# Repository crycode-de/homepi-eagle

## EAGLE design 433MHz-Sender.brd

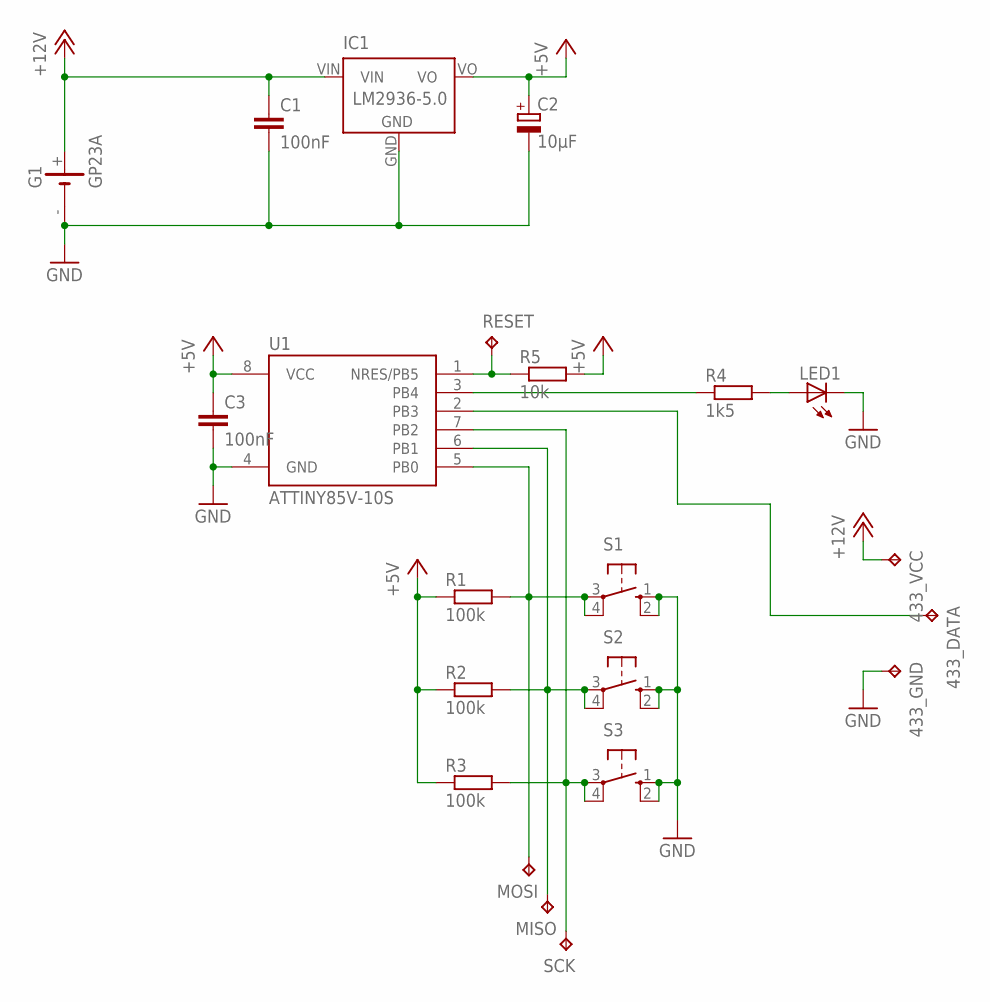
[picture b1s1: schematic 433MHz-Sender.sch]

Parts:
433_DATA, 433_GND, 433_VCC: TPPAD1-13; P1-13
C1, C3: 100nF; C025-025X050
C2: 10µF; E2-4
G1: GP23A
IC1: LM2936-5.0; TO92-INLINE
LED1: LED3MM
MISO: TPPAD1-13; P1-13
MOSI: TPPAD1-13; P1-13
R1, R2, R3: 100k; 0204/5
R4: 1k5; 0204/5
R5: 10k; 0204/5
RESET: TPPAD1-13; P1-13
S1, S2, S3: 10-XX; B3F-10XX
SCK: TPPAD1-13; P1-13
U1: ATTINY85V-10S; SOIC8_EIAJ_208MIL

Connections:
+5V: C2.+, C3.1, IC1.VO, R1.1, R2.1, R3.1, R5.2, U1.8 (VCC)
+12V: 433_VCC.TP, C1.1, G1.+, IC1.VIN
GND: 433_GND.TP, C1.2, C2.-, C3.2, G1.-, IC1.GND, LED1.K (C), S1.1 (S), S1.2 (S1), S2.1 (S), S2.2 (S1), S3.1 (S), S3.2 (S1), U1.4 (GND)
unnamed: 433_DATA.TP, U1.2 (PB3)
unnamed: R5.1, RESET.TP, U1.1 (NRES/PB5)
unnamed: MOSI.TP, R1.2, S1.3, S1.4 (P1), U1.5 (PB0)
unnamed: MISO.TP, R2.2, S2.3, S2.4 (P1), U1.6 (PB1)
unnamed: R3.2, S3.3, S3.4 (P1), SCK.TP, U1.7 (PB2)
unnamed: R4.1, U1.3 (PB4)
unnamed: LED1.A, R4.2

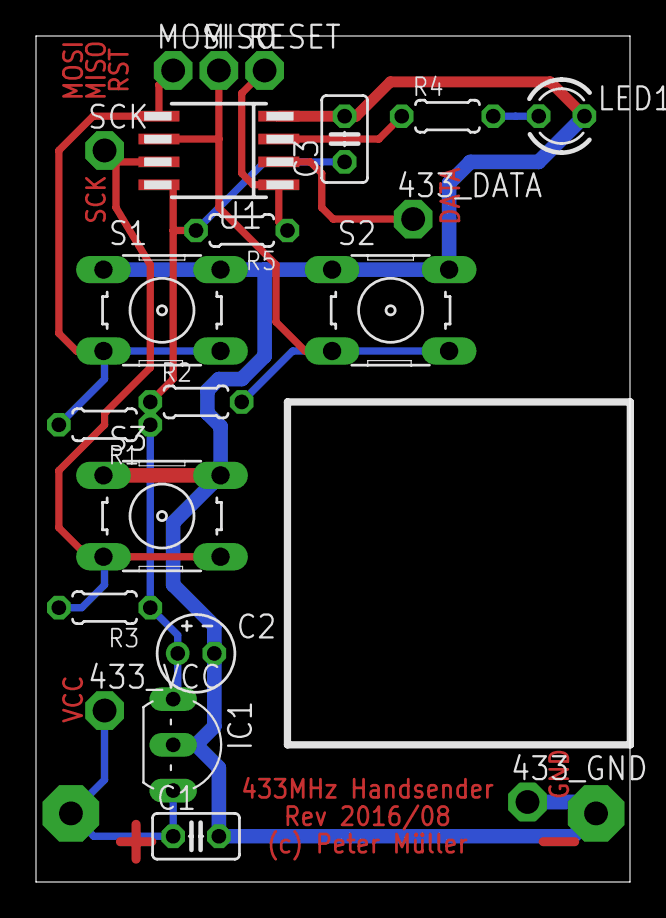
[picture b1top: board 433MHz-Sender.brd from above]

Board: 2 copper layers, 33.0 x 47.0 mm, 22 parts (1 on the bottom side), 10 nets.

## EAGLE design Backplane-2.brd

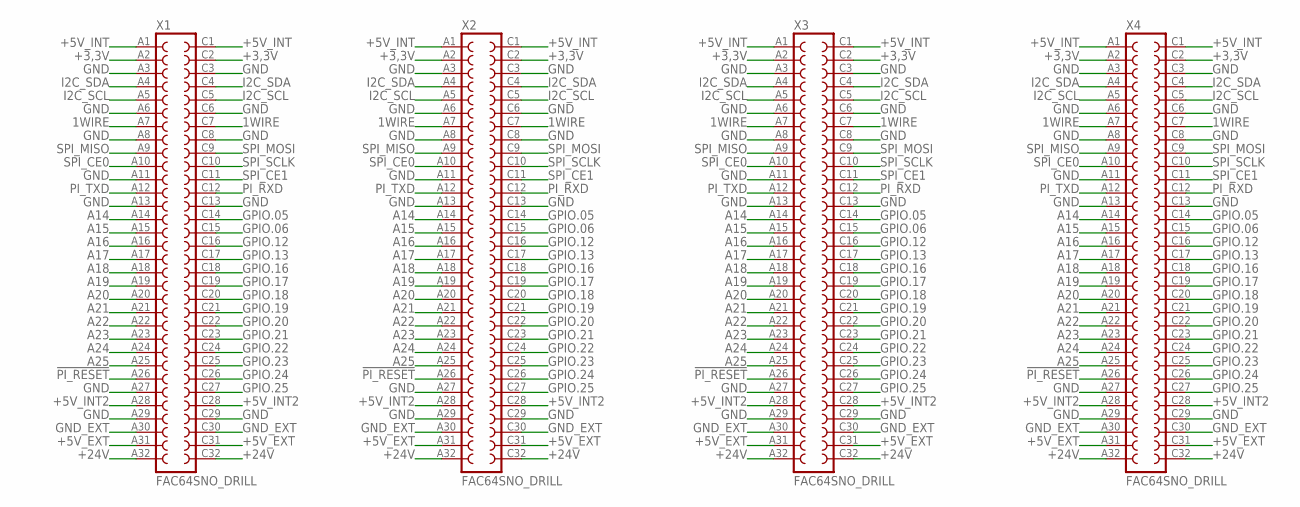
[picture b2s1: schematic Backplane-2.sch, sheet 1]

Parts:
X1, X2, X3, X4: FAC64SNO_DRILL; FAC64S_NO_DRILL

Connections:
1WIRE: X1.A7, X1.C7, X2.A7, X2.C7, X3.A7, X3.C7, X4.A7, X4.C7; also elsewhere on the board
!PI_RESET: X1.A26, X2.A26, X3.A26, X4.A26; also elsewhere on the board
+3,3V: X1.A2, X1.C2, X2.A2, X2.C2, X3.A2, X3.C2, X4.A2, X4.C2; also elsewhere on the board
+5V_EXT: X1.A31, X1.C31, X2.A31, X2.C31, X3.A31, X3.C31, X4.A31, X4.C31; also elsewhere on the board
+5V_INT: X1.A1, X1.C1, X2.A1, X2.C1, X3.A1, X3.C1, X4.A1, X4.C1; also elsewhere on the board
+5V_INT2: X1.A28, X1.C28, X2.A28, X2.C28, X3.A28, X3.C28, X4.A28, X4.C28; also elsewhere on the board
+24V: X1.A32, X1.C32, X2.A32, X2.C32, X3.A32, X3.C32, X4.A32, X4.C32; also elsewhere on the board
A14: X1.A14, X2.A14, X3.A14, X4.A14; also elsewhere on the board
A15: X1.A15, X2.A15, X3.A15, X4.A15; also elsewhere on the board
A16: X1.A16, X2.A16, X3.A16, X4.A16; also elsewhere on the board
A17: X1.A17, X2.A17, X3.A17, X4.A17; also elsewhere on the board
A18: X1.A18, X2.A18, X3.A18, X4.A18; also elsewhere on the board
A19: X1.A19, X2.A19, X3.A19, X4.A19; also elsewhere on the board
A20: X1.A20, X2.A20, X3.A20, X4.A20; also elsewhere on the board
A21: X1.A21, X2.A21, X3.A21, X4.A21; also elsewhere on the board
A22: X1.A22, X2.A22, X3.A22, X4.A22; also elsewhere on the board
A23: X1.A23, X2.A23, X3.A23, X4.A23; also elsewhere on the board
A24: X1.A24, X2.A24, X3.A24, X4.A24; also elsewhere on the board
A25: X1.A25, X2.A25, X3.A25, X4.A25; also elsewhere on the board
GND: X1.A3, X1.A6, X1.A8, X1.A11, X1.A13, X1.A27, X1.A29, X1.C3, X1.C6, X1.C8, X1.C13, X1.C29, X2.A3, X2.A6, X2.A8, X2.A11, X2.A13, X2.A27, X2.A29, X2.C3, X2.C6, X2.C8, X2.C13, X2.C29, X3.A3, X3.A6, X3.A8, X3.A11, X3.A13, X3.A27, X3.A29, X3.C3, X3.C6, X3.C8, X3.C13, X3.C29, X4.A3, X4.A6, X4.A8, X4.A11, X4.A13, X4.A27, X4.A29, X4.C3, X4.C6, X4.C8, X4.C13, X4.C29; also elsewhere on the board
GND_EXT: X1.A30, X1.C30, X2.A30, X2.C30, X3.A30, X3.C30, X4.A30, X4.C30; also elsewhere on the board
GPIO.05: X1.C14, X2.C14, X3.C14, X4.C14; also elsewhere on the board
GPIO.06: X1.C15, X2.C15, X3.C15, X4.C15; also elsewhere on the board
GPIO.12: X1.C16, X2.C16, X3.C16, X4.C16; also elsewhere on the board
GPIO.13: X1.C17, X2.C17, X3.C17, X4.C17; also elsewhere on the board
GPIO.16: X1.C18, X2.C18, X3.C18, X4.C18; also elsewhere on the board
GPIO.17: X1.C19, X2.C19, X3.C19, X4.C19; also elsewhere on the board
GPIO.18: X1.C20, X2.C20, X3.C20, X4.C20; also elsewhere on the board
GPIO.19: X1.C21, X2.C21, X3.C21, X4.C21; also elsewhere on the board
GPIO.20: X1.C22, X2.C22, X3.C22, X4.C22; also elsewhere on the board
GPIO.21: X1.C23, X2.C23, X3.C23, X4.C23; also elsewhere on the board
GPIO.22: X1.C24, X2.C24, X3.C24, X4.C24; also elsewhere on the board
GPIO.23: X1.C25, X2.C25, X3.C25, X4.C25; also elsewhere on the board
GPIO.24: X1.C26, X2.C26, X3.C26, X4.C26; also elsewhere on the board
GPIO.25: X1.C27, X2.C27, X3.C27, X4.C27; also elsewhere on the board
I2C_SCL: X1.A5, X1.C5, X2.A5, X2.C5, X3.A5, X3.C5, X4.A5, X4.C5; also elsewhere on the board
I2C_SDA: X1.A4, X1.C4, X2.A4, X2.C4, X3.A4, X3.C4, X4.A4, X4.C4; also elsewhere on the board
PI_RXD: X1.C12, X2.C12, X3.C12, X4.C12; also elsewhere on the board
PI_TXD: X1.A12, X2.A12, X3.A12, X4.A12; also elsewhere on the board
SPI_CE0: X1.A10, X2.A10, X3.A10, X4.A10; also elsewhere on the board
SPI_CE1: X1.C11, X2.C11, X3.C11, X4.C11; also elsewhere on the board
SPI_MISO: X1.A9, X2.A9, X3.A9, X4.A9; also elsewhere on the board
SPI_MOSI: X1.C9, X2.C9, X3.C9, X4.C9; also elsewhere on the board
SPI_SCLK: X1.C10, X2.C10, X3.C10, X4.C10; also elsewhere on the board

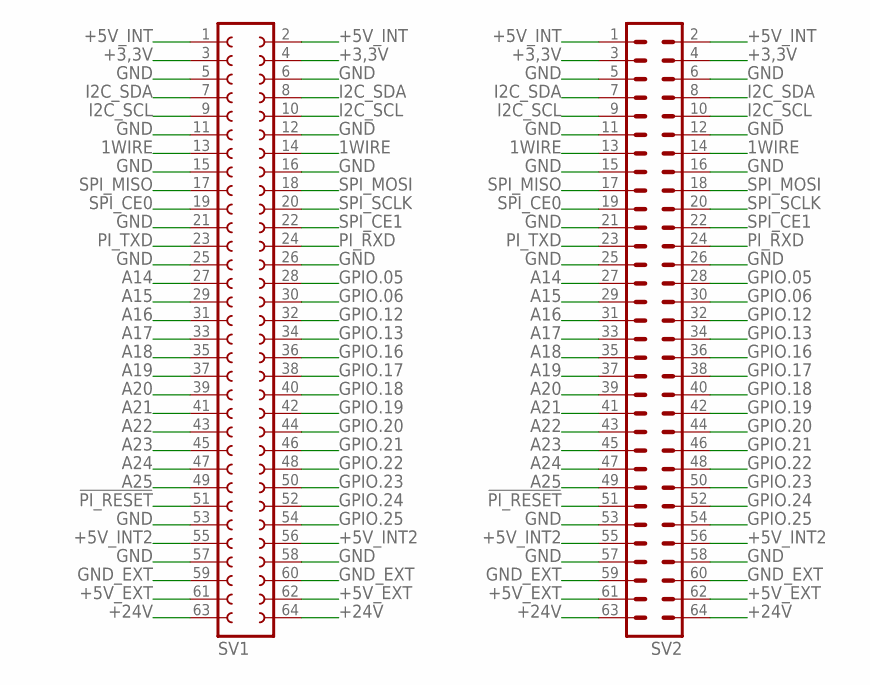
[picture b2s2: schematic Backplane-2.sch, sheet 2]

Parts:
SV1: FE32-2W
SV2: MA32-2W

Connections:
1WIRE: SV1.13, SV1.14, SV2.13, SV2.14; also elsewhere on the board
!PI_RESET: SV1.51, SV2.51; also elsewhere on the board
+3,3V: SV1.3, SV1.4, SV2.3, SV2.4; also elsewhere on the board
+5V_EXT: SV1.61, SV1.62, SV2.61, SV2.62; also elsewhere on the board
+5V_INT: SV1.1, SV1.2, SV2.1, SV2.2; also elsewhere on the board
+5V_INT2: SV1.55, SV1.56, SV2.55, SV2.56; also elsewhere on the board
+24V: SV1.63, SV1.64, SV2.63, SV2.64; also elsewhere on the board
A14: SV1.27, SV2.27; also elsewhere on the board
A15: SV1.29, SV2.29; also elsewhere on the board
A16: SV1.31, SV2.31; also elsewhere on the board
A17: SV1.33, SV2.33; also elsewhere on the board
A18: SV1.35, SV2.35; also elsewhere on the board
A19: SV1.37, SV2.37; also elsewhere on the board
A20: SV1.39, SV2.39; also elsewhere on the board
A21: SV1.41, SV2.41; also elsewhere on the board
A22: SV1.43, SV2.43; also elsewhere on the board
A23: SV1.45, SV2.45; also elsewhere on the board
A24: SV1.47, SV2.47; also elsewhere on the board
A25: SV1.49, SV2.49; also elsewhere on the board
GND: SV1.5, SV1.6, SV1.11, SV1.12, SV1.15, SV1.16, SV1.21, SV1.25, SV1.26, SV1.53, SV1.57, SV1.58, SV2.5, SV2.6, SV2.11, SV2.12, SV2.15, SV2.16, SV2.21, SV2.25, SV2.26, SV2.53, SV2.57, SV2.58; also elsewhere on the board
GND_EXT: SV1.59, SV1.60, SV2.59, SV2.60; also elsewhere on the board
GPIO.05: SV1.28, SV2.28; also elsewhere on the board
GPIO.06: SV1.30, SV2.30; also elsewhere on the board
GPIO.12: SV1.32, SV2.32; also elsewhere on the board
GPIO.13: SV1.34, SV2.34; also elsewhere on the board
GPIO.16: SV1.36, SV2.36; also elsewhere on the board
GPIO.17: SV1.38, SV2.38; also elsewhere on the board
GPIO.18: SV1.40, SV2.40; also elsewhere on the board
GPIO.19: SV1.42, SV2.42; also elsewhere on the board
GPIO.20: SV1.44, SV2.44; also elsewhere on the board
GPIO.21: SV1.46, SV2.46; also elsewhere on the board
GPIO.22: SV1.48, SV2.48; also elsewhere on the board
GPIO.23: SV1.50, SV2.50; also elsewhere on the board
GPIO.24: SV1.52, SV2.52; also elsewhere on the board
GPIO.25: SV1.54, SV2.54; also elsewhere on the board
I2C_SCL: SV1.9, SV1.10, SV2.9, SV2.10; also elsewhere on the board
I2C_SDA: SV1.7, SV1.8, SV2.7, SV2.8; also elsewhere on the board
PI_RXD: SV1.24, SV2.24; also elsewhere on the board
PI_TXD: SV1.23, SV2.23; also elsewhere on the board
SPI_CE0: SV1.19, SV2.19; also elsewhere on the board
SPI_CE1: SV1.22, SV2.22; also elsewhere on the board
SPI_MISO: SV1.17, SV2.17; also elsewhere on the board
SPI_MOSI: SV1.18, SV2.18; also elsewhere on the board
SPI_SCLK: SV1.20, SV2.20; also elsewhere on the board

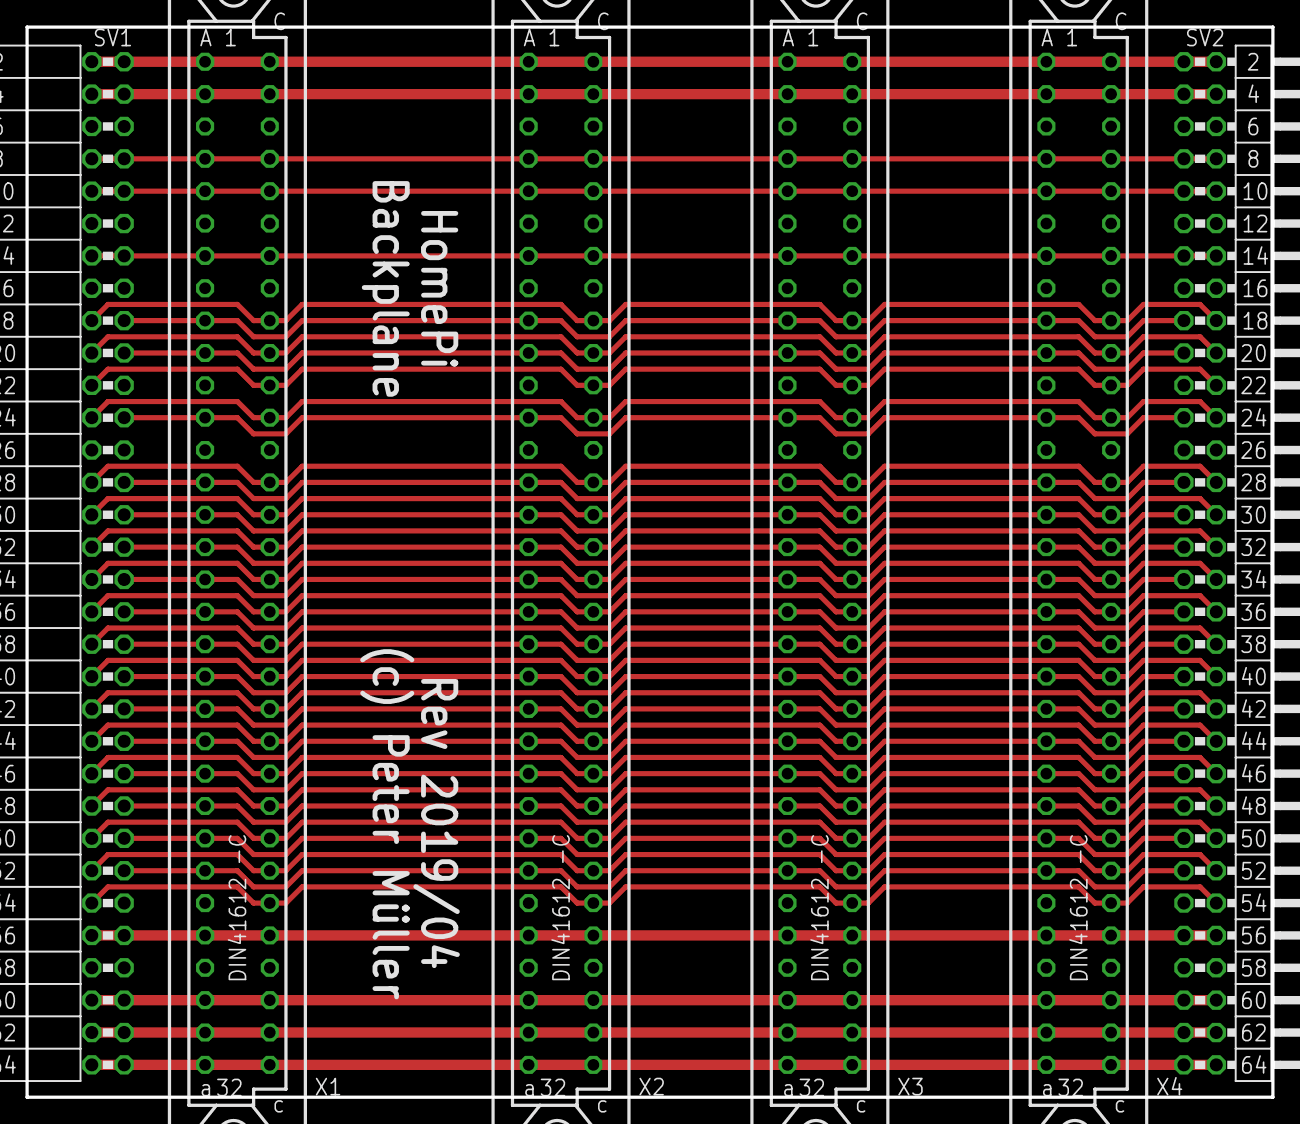
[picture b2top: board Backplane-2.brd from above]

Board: 2 copper layers, 97.8 x 84.0 mm, 6 parts (0 on the bottom side), 44 nets.

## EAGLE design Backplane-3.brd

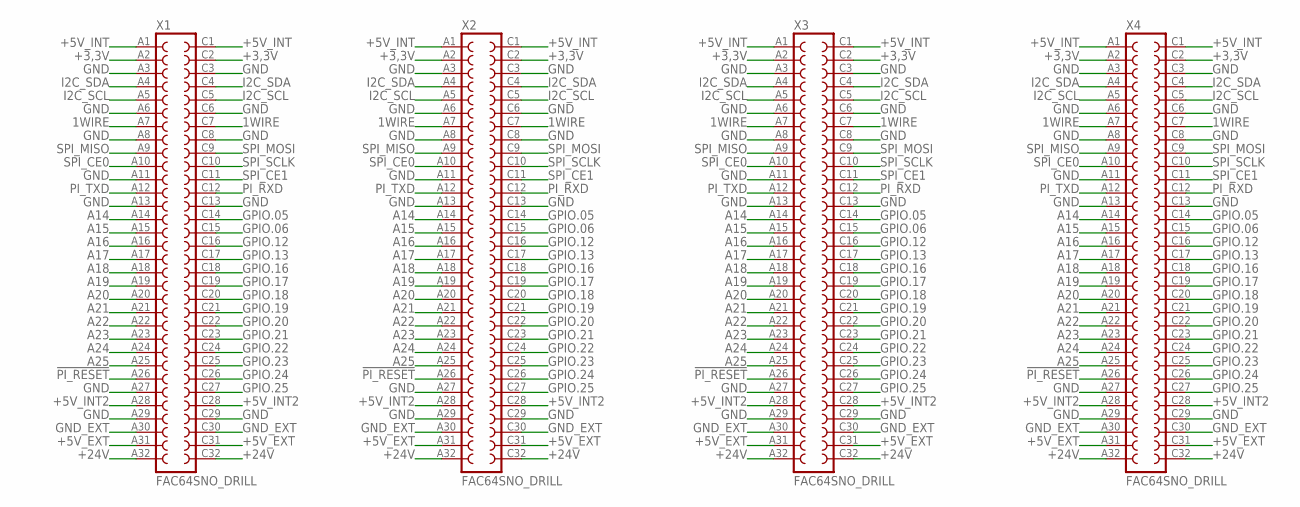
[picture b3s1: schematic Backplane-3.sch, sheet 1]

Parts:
X1, X2, X3, X4: FAC64SNO_DRILL; FAC64S_NO_DRILL

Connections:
1WIRE: X1.A7, X1.C7, X2.A7, X2.C7, X3.A7, X3.C7, X4.A7, X4.C7; also elsewhere on the board
!PI_RESET: X1.A26, X2.A26, X3.A26, X4.A26; also elsewhere on the board
+3,3V: X1.A2, X1.C2, X2.A2, X2.C2, X3.A2, X3.C2, X4.A2, X4.C2; also elsewhere on the board
+5V_EXT: X1.A31, X1.C31, X2.A31, X2.C31, X3.A31, X3.C31, X4.A31, X4.C31; also elsewhere on the board
+5V_INT: X1.A1, X1.C1, X2.A1, X2.C1, X3.A1, X3.C1, X4.A1, X4.C1; also elsewhere on the board
+5V_INT2: X1.A28, X1.C28, X2.A28, X2.C28, X3.A28, X3.C28, X4.A28, X4.C28; also elsewhere on the board
+24V: X1.A32, X1.C32, X2.A32, X2.C32, X3.A32, X3.C32, X4.A32, X4.C32; also elsewhere on the board
A14: X1.A14, X2.A14, X3.A14, X4.A14; also elsewhere on the board
A15: X1.A15, X2.A15, X3.A15, X4.A15; also elsewhere on the board
A16: X1.A16, X2.A16, X3.A16, X4.A16; also elsewhere on the board
A17: X1.A17, X2.A17, X3.A17, X4.A17; also elsewhere on the board
A18: X1.A18, X2.A18, X3.A18, X4.A18; also elsewhere on the board
A19: X1.A19, X2.A19, X3.A19, X4.A19; also elsewhere on the board
A20: X1.A20, X2.A20, X3.A20, X4.A20; also elsewhere on the board
A21: X1.A21, X2.A21, X3.A21, X4.A21; also elsewhere on the board
A22: X1.A22, X2.A22, X3.A22, X4.A22; also elsewhere on the board
A23: X1.A23, X2.A23, X3.A23, X4.A23; also elsewhere on the board
A24: X1.A24, X2.A24, X3.A24, X4.A24; also elsewhere on the board
A25: X1.A25, X2.A25, X3.A25, X4.A25; also elsewhere on the board
GND: X1.A3, X1.A6, X1.A8, X1.A11, X1.A13, X1.A27, X1.A29, X1.C3, X1.C6, X1.C8, X1.C13, X1.C29, X2.A3, X2.A6, X2.A8, X2.A11, X2.A13, X2.A27, X2.A29, X2.C3, X2.C6, X2.C8, X2.C13, X2.C29, X3.A3, X3.A6, X3.A8, X3.A11, X3.A13, X3.A27, X3.A29, X3.C3, X3.C6, X3.C8, X3.C13, X3.C29, X4.A3, X4.A6, X4.A8, X4.A11, X4.A13, X4.A27, X4.A29, X4.C3, X4.C6, X4.C8, X4.C13, X4.C29; also elsewhere on the board
GND_EXT: X1.A30, X1.C30, X2.A30, X2.C30, X3.A30, X3.C30, X4.A30, X4.C30; also elsewhere on the board
GPIO.05: X1.C14, X2.C14, X3.C14, X4.C14; also elsewhere on the board
GPIO.06: X1.C15, X2.C15, X3.C15, X4.C15; also elsewhere on the board
GPIO.12: X1.C16, X2.C16, X3.C16, X4.C16; also elsewhere on the board
GPIO.13: X1.C17, X2.C17, X3.C17, X4.C17; also elsewhere on the board
GPIO.16: X1.C18, X2.C18, X3.C18, X4.C18; also elsewhere on the board
GPIO.17: X1.C19, X2.C19, X3.C19, X4.C19; also elsewhere on the board
GPIO.18: X1.C20, X2.C20, X3.C20, X4.C20; also elsewhere on the board
GPIO.19: X1.C21, X2.C21, X3.C21, X4.C21; also elsewhere on the board
GPIO.20: X1.C22, X2.C22, X3.C22, X4.C22; also elsewhere on the board
GPIO.21: X1.C23, X2.C23, X3.C23, X4.C23; also elsewhere on the board
GPIO.22: X1.C24, X2.C24, X3.C24, X4.C24; also elsewhere on the board
GPIO.23: X1.C25, X2.C25, X3.C25, X4.C25; also elsewhere on the board
GPIO.24: X1.C26, X2.C26, X3.C26, X4.C26; also elsewhere on the board
GPIO.25: X1.C27, X2.C27, X3.C27, X4.C27; also elsewhere on the board
I2C_SCL: X1.A5, X1.C5, X2.A5, X2.C5, X3.A5, X3.C5, X4.A5, X4.C5; also elsewhere on the board
I2C_SDA: X1.A4, X1.C4, X2.A4, X2.C4, X3.A4, X3.C4, X4.A4, X4.C4; also elsewhere on the board
PI_RXD: X1.C12, X2.C12, X3.C12, X4.C12; also elsewhere on the board
PI_TXD: X1.A12, X2.A12, X3.A12, X4.A12; also elsewhere on the board
SPI_CE0: X1.A10, X2.A10, X3.A10, X4.A10; also elsewhere on the board
SPI_CE1: X1.C11, X2.C11, X3.C11, X4.C11; also elsewhere on the board
SPI_MISO: X1.A9, X2.A9, X3.A9, X4.A9; also elsewhere on the board
SPI_MOSI: X1.C9, X2.C9, X3.C9, X4.C9; also elsewhere on the board
SPI_SCLK: X1.C10, X2.C10, X3.C10, X4.C10; also elsewhere on the board

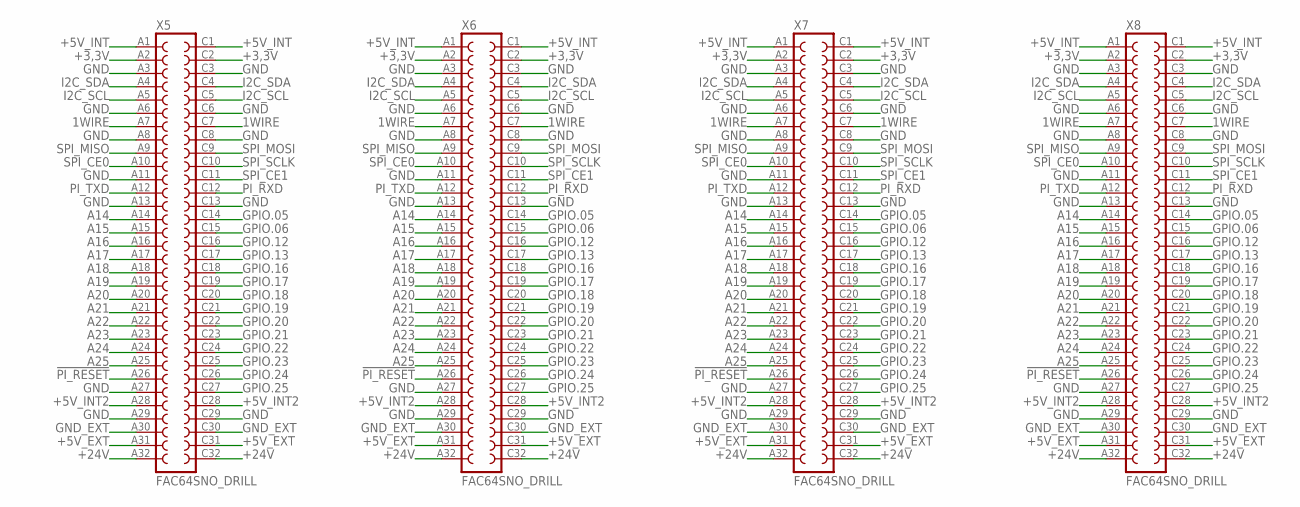
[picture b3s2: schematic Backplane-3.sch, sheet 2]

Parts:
X5, X6, X7, X8: FAC64SNO_DRILL; FAC64S_NO_DRILL

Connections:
1WIRE: X5.A7, X5.C7, X6.A7, X6.C7, X7.A7, X7.C7, X8.A7, X8.C7; also elsewhere on the board
!PI_RESET: X5.A26, X6.A26, X7.A26, X8.A26; also elsewhere on the board
+3,3V: X5.A2, X5.C2, X6.A2, X6.C2, X7.A2, X7.C2, X8.A2, X8.C2; also elsewhere on the board
+5V_EXT: X5.A31, X5.C31, X6.A31, X6.C31, X7.A31, X7.C31, X8.A31, X8.C31; also elsewhere on the board
+5V_INT: X5.A1, X5.C1, X6.A1, X6.C1, X7.A1, X7.C1, X8.A1, X8.C1; also elsewhere on the board
+5V_INT2: X5.A28, X5.C28, X6.A28, X6.C28, X7.A28, X7.C28, X8.A28, X8.C28; also elsewhere on the board
+24V: X5.A32, X5.C32, X6.A32, X6.C32, X7.A32, X7.C32, X8.A32, X8.C32; also elsewhere on the board
A14: X5.A14, X6.A14, X7.A14, X8.A14; also elsewhere on the board
A15: X5.A15, X6.A15, X7.A15, X8.A15; also elsewhere on the board
A16: X5.A16, X6.A16, X7.A16, X8.A16; also elsewhere on the board
A17: X5.A17, X6.A17, X7.A17, X8.A17; also elsewhere on the board
A18: X5.A18, X6.A18, X7.A18, X8.A18; also elsewhere on the board
A19: X5.A19, X6.A19, X7.A19, X8.A19; also elsewhere on the board
A20: X5.A20, X6.A20, X7.A20, X8.A20; also elsewhere on the board
A21: X5.A21, X6.A21, X7.A21, X8.A21; also elsewhere on the board
A22: X5.A22, X6.A22, X7.A22, X8.A22; also elsewhere on the board
A23: X5.A23, X6.A23, X7.A23, X8.A23; also elsewhere on the board
A24: X5.A24, X6.A24, X7.A24, X8.A24; also elsewhere on the board
A25: X5.A25, X6.A25, X7.A25, X8.A25; also elsewhere on the board
GND: X5.A3, X5.A6, X5.A8, X5.A11, X5.A13, X5.A27, X5.A29, X5.C3, X5.C6, X5.C8, X5.C13, X5.C29, X6.A3, X6.A6, X6.A8, X6.A11, X6.A13, X6.A27, X6.A29, X6.C3, X6.C6, X6.C8, X6.C13, X6.C29, X7.A3, X7.A6, X7.A8, X7.A11, X7.A13, X7.A27, X7.A29, X7.C3, X7.C6, X7.C8, X7.C13, X7.C29, X8.A3, X8.A6, X8.A8, X8.A11, X8.A13, X8.A27, X8.A29, X8.C3, X8.C6, X8.C8, X8.C13, X8.C29; also elsewhere on the board
GND_EXT: X5.A30, X5.C30, X6.A30, X6.C30, X7.A30, X7.C30, X8.A30, X8.C30; also elsewhere on the board
GPIO.05: X5.C14, X6.C14, X7.C14, X8.C14; also elsewhere on the board
GPIO.06: X5.C15, X6.C15, X7.C15, X8.C15; also elsewhere on the board
GPIO.12: X5.C16, X6.C16, X7.C16, X8.C16; also elsewhere on the board
GPIO.13: X5.C17, X6.C17, X7.C17, X8.C17; also elsewhere on the board
GPIO.16: X5.C18, X6.C18, X7.C18, X8.C18; also elsewhere on the board
GPIO.17: X5.C19, X6.C19, X7.C19, X8.C19; also elsewhere on the board
GPIO.18: X5.C20, X6.C20, X7.C20, X8.C20; also elsewhere on the board
GPIO.19: X5.C21, X6.C21, X7.C21, X8.C21; also elsewhere on the board
GPIO.20: X5.C22, X6.C22, X7.C22, X8.C22; also elsewhere on the board
GPIO.21: X5.C23, X6.C23, X7.C23, X8.C23; also elsewhere on the board
GPIO.22: X5.C24, X6.C24, X7.C24, X8.C24; also elsewhere on the board
GPIO.23: X5.C25, X6.C25, X7.C25, X8.C25; also elsewhere on the board
GPIO.24: X5.C26, X6.C26, X7.C26, X8.C26; also elsewhere on the board
GPIO.25: X5.C27, X6.C27, X7.C27, X8.C27; also elsewhere on the board
I2C_SCL: X5.A5, X5.C5, X6.A5, X6.C5, X7.A5, X7.C5, X8.A5, X8.C5; also elsewhere on the board
I2C_SDA: X5.A4, X5.C4, X6.A4, X6.C4, X7.A4, X7.C4, X8.A4, X8.C4; also elsewhere on the board
PI_RXD: X5.C12, X6.C12, X7.C12, X8.C12; also elsewhere on the board
PI_TXD: X5.A12, X6.A12, X7.A12, X8.A12; also elsewhere on the board
SPI_CE0: X5.A10, X6.A10, X7.A10, X8.A10; also elsewhere on the board
SPI_CE1: X5.C11, X6.C11, X7.C11, X8.C11; also elsewhere on the board
SPI_MISO: X5.A9, X6.A9, X7.A9, X8.A9; also elsewhere on the board
SPI_MOSI: X5.C9, X6.C9, X7.C9, X8.C9; also elsewhere on the board
SPI_SCLK: X5.C10, X6.C10, X7.C10, X8.C10; also elsewhere on the board

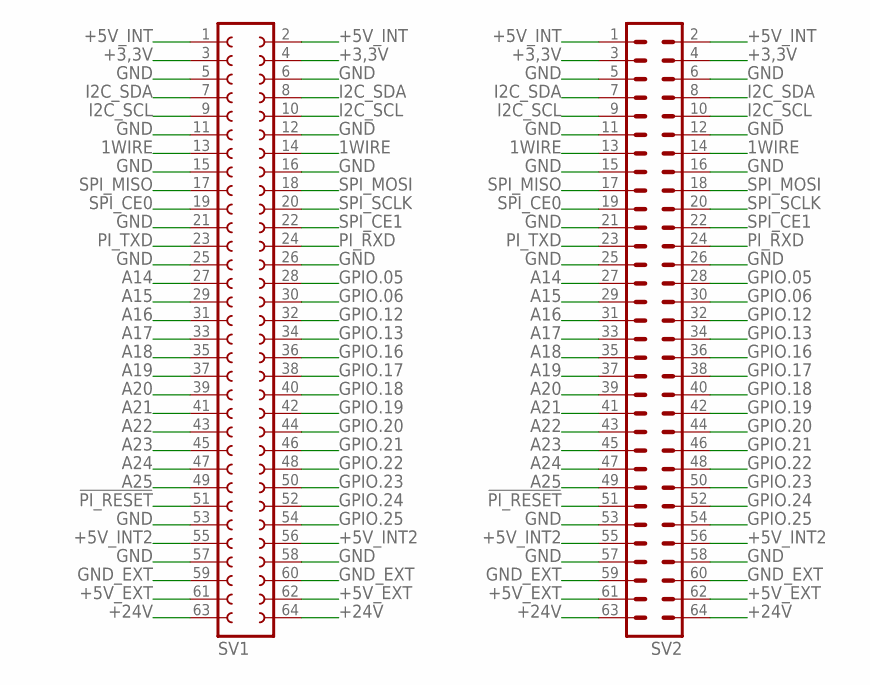
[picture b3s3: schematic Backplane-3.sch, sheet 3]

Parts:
SV1: FE32-2W
SV2: MA32-2W

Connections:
1WIRE: SV1.13, SV1.14, SV2.13, SV2.14; also elsewhere on the board
!PI_RESET: SV1.51, SV2.51; also elsewhere on the board
+3,3V: SV1.3, SV1.4, SV2.3, SV2.4; also elsewhere on the board
+5V_EXT: SV1.61, SV1.62, SV2.61, SV2.62; also elsewhere on the board
+5V_INT: SV1.1, SV1.2, SV2.1, SV2.2; also elsewhere on the board
+5V_INT2: SV1.55, SV1.56, SV2.55, SV2.56; also elsewhere on the board
+24V: SV1.63, SV1.64, SV2.63, SV2.64; also elsewhere on the board
A14: SV1.27, SV2.27; also elsewhere on the board
A15: SV1.29, SV2.29; also elsewhere on the board
A16: SV1.31, SV2.31; also elsewhere on the board
A17: SV1.33, SV2.33; also elsewhere on the board
A18: SV1.35, SV2.35; also elsewhere on the board
A19: SV1.37, SV2.37; also elsewhere on the board
A20: SV1.39, SV2.39; also elsewhere on the board
A21: SV1.41, SV2.41; also elsewhere on the board
A22: SV1.43, SV2.43; also elsewhere on the board
A23: SV1.45, SV2.45; also elsewhere on the board
A24: SV1.47, SV2.47; also elsewhere on the board
A25: SV1.49, SV2.49; also elsewhere on the board
GND: SV1.5, SV1.6, SV1.11, SV1.12, SV1.15, SV1.16, SV1.21, SV1.25, SV1.26, SV1.53, SV1.57, SV1.58, SV2.5, SV2.6, SV2.11, SV2.12, SV2.15, SV2.16, SV2.21, SV2.25, SV2.26, SV2.53, SV2.57, SV2.58; also elsewhere on the board
GND_EXT: SV1.59, SV1.60, SV2.59, SV2.60; also elsewhere on the board
GPIO.05: SV1.28, SV2.28; also elsewhere on the board
GPIO.06: SV1.30, SV2.30; also elsewhere on the board
GPIO.12: SV1.32, SV2.32; also elsewhere on the board
GPIO.13: SV1.34, SV2.34; also elsewhere on the board
GPIO.16: SV1.36, SV2.36; also elsewhere on the board
GPIO.17: SV1.38, SV2.38; also elsewhere on the board
GPIO.18: SV1.40, SV2.40; also elsewhere on the board
GPIO.19: SV1.42, SV2.42; also elsewhere on the board
GPIO.20: SV1.44, SV2.44; also elsewhere on the board
GPIO.21: SV1.46, SV2.46; also elsewhere on the board
GPIO.22: SV1.48, SV2.48; also elsewhere on the board
GPIO.23: SV1.50, SV2.50; also elsewhere on the board
GPIO.24: SV1.52, SV2.52; also elsewhere on the board
GPIO.25: SV1.54, SV2.54; also elsewhere on the board
I2C_SCL: SV1.9, SV1.10, SV2.9, SV2.10; also elsewhere on the board
I2C_SDA: SV1.7, SV1.8, SV2.7, SV2.8; also elsewhere on the board
PI_RXD: SV1.24, SV2.24; also elsewhere on the board
PI_TXD: SV1.23, SV2.23; also elsewhere on the board
SPI_CE0: SV1.19, SV2.19; also elsewhere on the board
SPI_CE1: SV1.22, SV2.22; also elsewhere on the board
SPI_MISO: SV1.17, SV2.17; also elsewhere on the board
SPI_MOSI: SV1.18, SV2.18; also elsewhere on the board
SPI_SCLK: SV1.20, SV2.20; also elsewhere on the board

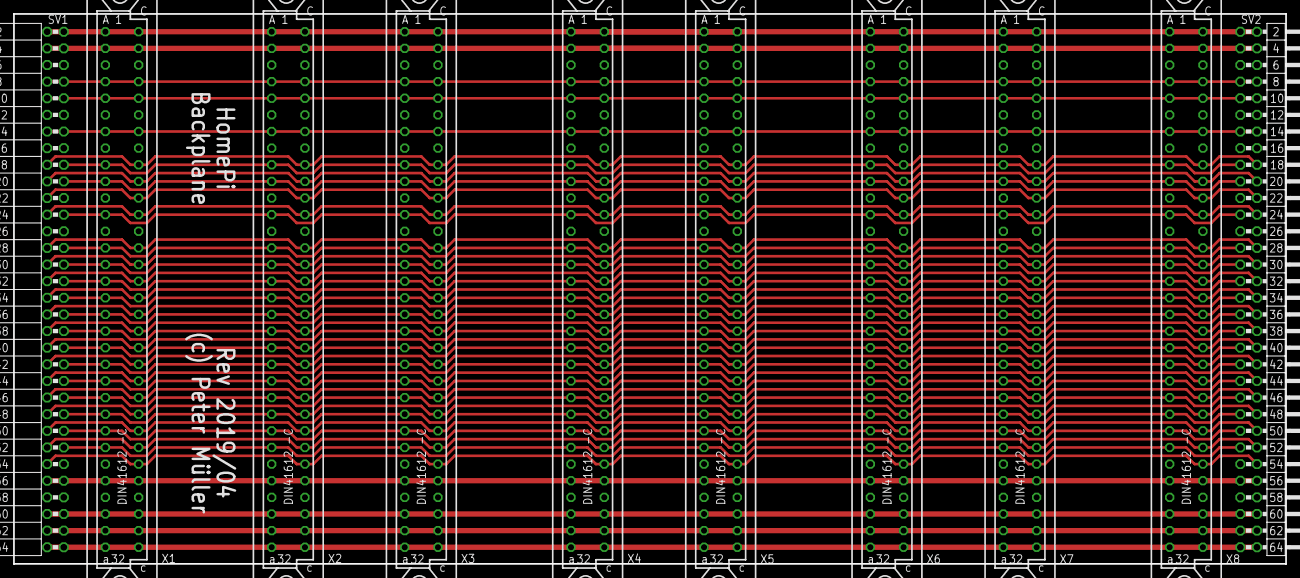
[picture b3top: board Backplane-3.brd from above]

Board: 2 copper layers, 194.3 x 84.0 mm, 10 parts (0 on the bottom side), 44 nets.

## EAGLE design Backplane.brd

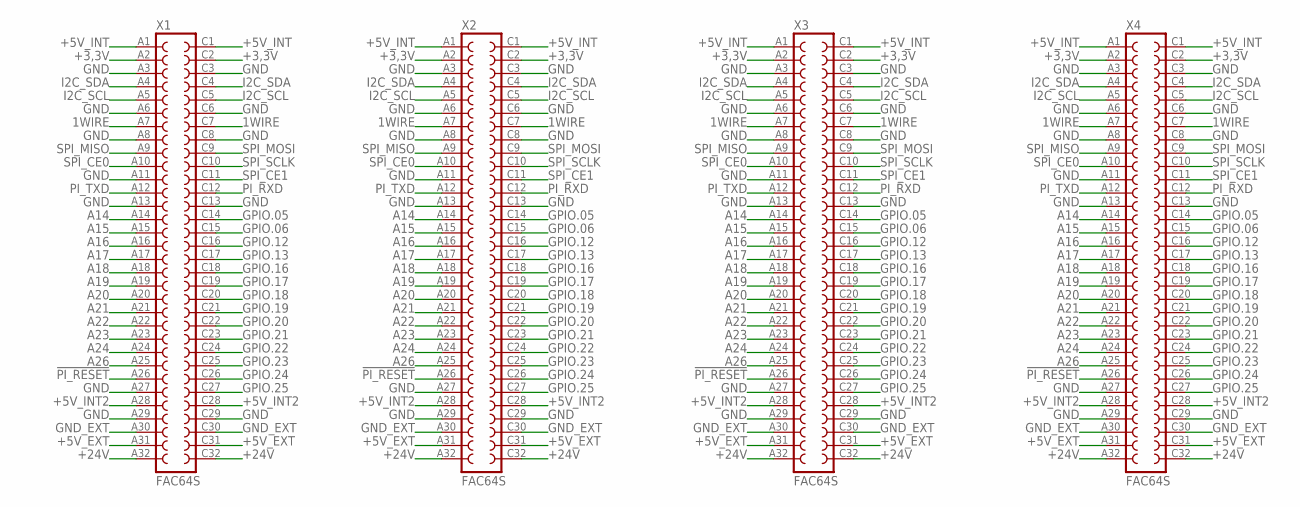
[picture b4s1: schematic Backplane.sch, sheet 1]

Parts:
X1, X2, X3, X4: FAC64S

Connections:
1WIRE: X1.A7, X1.C7, X2.A7, X2.C7, X3.A7, X3.C7, X4.A7, X4.C7; also elsewhere on the board
!PI_RESET: X1.A26, X2.A26, X3.A26, X4.A26; also elsewhere on the board
+3,3V: X1.A2, X1.C2, X2.A2, X2.C2, X3.A2, X3.C2, X4.A2, X4.C2; also elsewhere on the board
+5V_EXT: X1.A31, X1.C31, X2.A31, X2.C31, X3.A31, X3.C31, X4.A31, X4.C31; also elsewhere on the board
+5V_INT: X1.A1, X1.C1, X2.A1, X2.C1, X3.A1, X3.C1, X4.A1, X4.C1; also elsewhere on the board
+5V_INT2: X1.A28, X1.C28, X2.A28, X2.C28, X3.A28, X3.C28, X4.A28, X4.C28; also elsewhere on the board
+24V: X1.A32, X1.C32, X2.A32, X2.C32, X3.A32, X3.C32, X4.A32, X4.C32; also elsewhere on the board
A14: X1.A14, X2.A14, X3.A14, X4.A14; also elsewhere on the board
A15: X1.A15, X2.A15, X3.A15, X4.A15; also elsewhere on the board
A16: X1.A16, X2.A16, X3.A16, X4.A16; also elsewhere on the board
A17: X1.A17, X2.A17, X3.A17, X4.A17; also elsewhere on the board
A18: X1.A18, X2.A18, X3.A18, X4.A18; also elsewhere on the board
A19: X1.A19, X2.A19, X3.A19, X4.A19; also elsewhere on the board
A20: X1.A20, X2.A20, X3.A20, X4.A20; also elsewhere on the board
A21: X1.A21, X2.A21, X3.A21, X4.A21; also elsewhere on the board
A22: X1.A22, X2.A22, X3.A22, X4.A22; also elsewhere on the board
A23: X1.A23, X2.A23, X3.A23, X4.A23; also elsewhere on the board
A24: X1.A24, X2.A24, X3.A24, X4.A24; also elsewhere on the board
A26: X1.A25, X2.A25, X3.A25, X4.A25; also elsewhere on the board
GND: X1.A3, X1.A6, X1.A8, X1.A11, X1.A13, X1.A27, X1.A29, X1.C3, X1.C6, X1.C8, X1.C13, X1.C29, X2.A3, X2.A6, X2.A8, X2.A11, X2.A13, X2.A27, X2.A29, X2.C3, X2.C6, X2.C8, X2.C13, X2.C29, X3.A3, X3.A6, X3.A8, X3.A11, X3.A13, X3.A27, X3.A29, X3.C3, X3.C6, X3.C8, X3.C13, X3.C29, X4.A3, X4.A6, X4.A8, X4.A11, X4.A13, X4.A27, X4.A29, X4.C3, X4.C6, X4.C8, X4.C13, X4.C29; also elsewhere on the board
GND_EXT: X1.A30, X1.C30, X2.A30, X2.C30, X3.A30, X3.C30, X4.A30, X4.C30; also elsewhere on the board
GPIO.05: X1.C14, X2.C14, X3.C14, X4.C14; also elsewhere on the board
GPIO.06: X1.C15, X2.C15, X3.C15, X4.C15; also elsewhere on the board
GPIO.12: X1.C16, X2.C16, X3.C16, X4.C16; also elsewhere on the board
GPIO.13: X1.C17, X2.C17, X3.C17, X4.C17; also elsewhere on the board
GPIO.16: X1.C18, X2.C18, X3.C18, X4.C18; also elsewhere on the board
GPIO.17: X1.C19, X2.C19, X3.C19, X4.C19; also elsewhere on the board
GPIO.18: X1.C20, X2.C20, X3.C20, X4.C20; also elsewhere on the board
GPIO.19: X1.C21, X2.C21, X3.C21, X4.C21; also elsewhere on the board
GPIO.20: X1.C22, X2.C22, X3.C22, X4.C22; also elsewhere on the board
GPIO.21: X1.C23, X2.C23, X3.C23, X4.C23; also elsewhere on the board
GPIO.22: X1.C24, X2.C24, X3.C24, X4.C24; also elsewhere on the board
GPIO.23: X1.C25, X2.C25, X3.C25, X4.C25; also elsewhere on the board
GPIO.24: X1.C26, X2.C26, X3.C26, X4.C26; also elsewhere on the board
GPIO.25: X1.C27, X2.C27, X3.C27, X4.C27; also elsewhere on the board
I2C_SCL: X1.A5, X1.C5, X2.A5, X2.C5, X3.A5, X3.C5, X4.A5, X4.C5; also elsewhere on the board
I2C_SDA: X1.A4, X1.C4, X2.A4, X2.C4, X3.A4, X3.C4, X4.A4, X4.C4; also elsewhere on the board
PI_RXD: X1.C12, X2.C12, X3.C12, X4.C12; also elsewhere on the board
PI_TXD: X1.A12, X2.A12, X3.A12, X4.A12; also elsewhere on the board
SPI_CE0: X1.A10, X2.A10, X3.A10, X4.A10; also elsewhere on the board
SPI_CE1: X1.C11, X2.C11, X3.C11, X4.C11; also elsewhere on the board
SPI_MISO: X1.A9, X2.A9, X3.A9, X4.A9; also elsewhere on the board
SPI_MOSI: X1.C9, X2.C9, X3.C9, X4.C9; also elsewhere on the board
SPI_SCLK: X1.C10, X2.C10, X3.C10, X4.C10; also elsewhere on the board
